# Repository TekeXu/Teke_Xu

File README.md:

Teke Xu
04/01/2016
April Fools' Day!

tama wei sm mei huan hang!!!

                                                    空山新雨后
                                                    天气晚来秋
                                                    明月松间照
                                                    清泉石上流

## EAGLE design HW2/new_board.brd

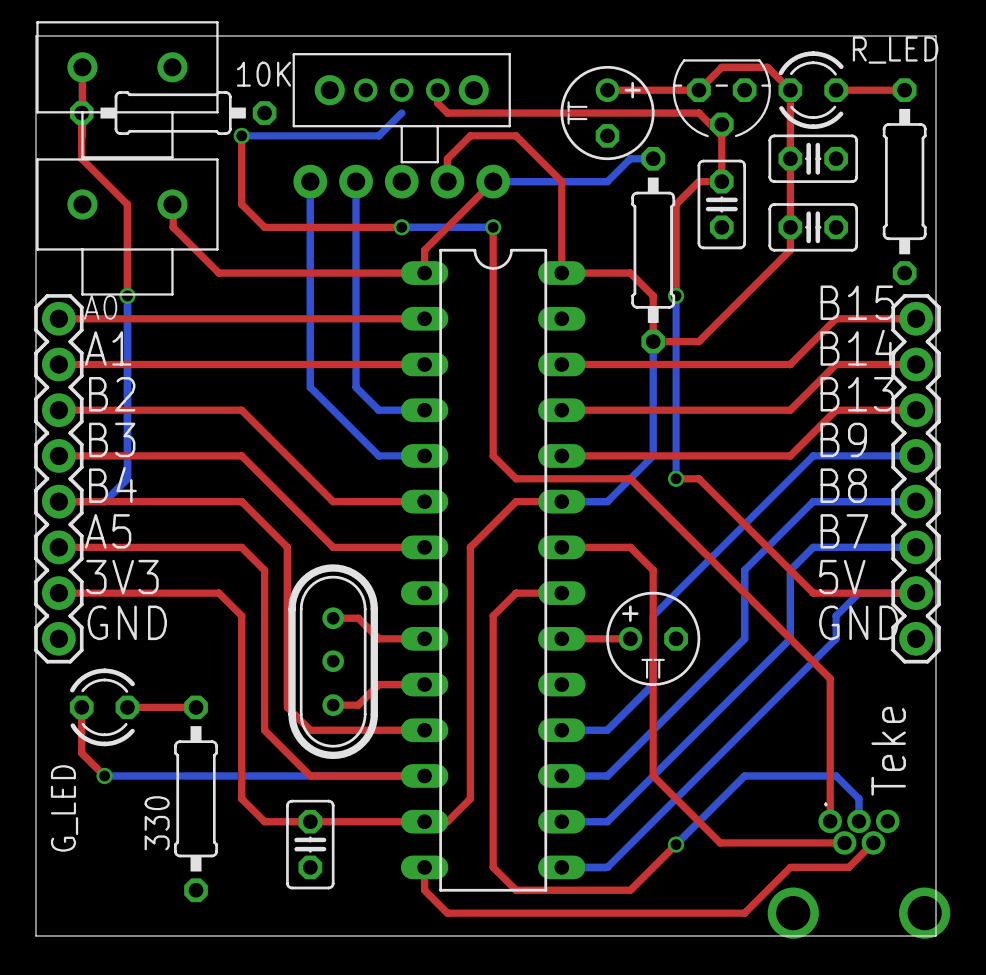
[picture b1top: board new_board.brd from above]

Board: 2 copper layers, 50.0 x 50.0 mm, 22 parts (0 on the bottom side), 27 nets.

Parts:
10K, 330: 0207/10
.: MINI_USB; USB-MB-H
C1, C3, C4, C5: 0.1uF; C025-025X050
C6, C7: 10uF; TT2D5
G_LED: LED3MM
J1: 1X05_NO_SILK
J2, J3: 1X08_ROUND
R2: 330; 0207/10
R4: 10K; 0207/10
R_LED: LED3MM
U$1: PIC32; DIL28-3
U$3: SLIDE_SWITCH
U$4, U$5: PUSH_BUTTON
U$9: MCP1702; TO92
X1: HC49-HC49-3L; HC49-3L

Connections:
+3V3: C1.1, C3.1, C4.1, C7.+, J1.2, J2.7, R4.1, R_LED.A, U$1.13, U$1.23, U$1.28, U$9.3
GND: 10K.2, 330.1, ..GND, C1.2, C3.2, C4.2, C5.2, C6.-, C7.-, J1.3, J2.8, J3.8, R2.1, U$1.8, U$1.19, U$1.27, U$4.P$2, U$5.P$1, U$9.1, X1.2
unnamed: ..ID, U$1.14
unnamed: J1.4, U$1.4
unnamed: J1.5, U$1.5
unnamed: U$1.9, X1.1
unnamed: U$1.10, X1.3
unnamed: 10K.1, J2.5, U$1.11, U$5.P$2
unnamed: R2.2, R_LED.K
unnamed: J1.1, R4.2, U$1.1, U$4.P$1
unnamed: C6.+, U$1.20
unnamed: 330.2, G_LED.K
unnamed: G_LED.A, J2.6, U$1.12
unnamed: ..VBUS, U$3.P$4
unnamed: C5.1, J3.7, U$1.15, U$3.P$3, U$9.2
unnamed: ..D-, U$1.22
unnamed: ..D+, U$1.21
unnamed: J2.1, U$1.2
unnamed: J2.2, U$1.3
unnamed: J2.3, U$1.6
unnamed: J2.4, U$1.7
unnamed: J3.1, U$1.26
unnamed: J3.2, U$1.25
unnamed: J3.3, U$1.24
unnamed: J3.4, U$1.18
unnamed: J3.5, U$1.17
unnamed: J3.6, U$1.16

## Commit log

2016-04-02 My first commit!
2016-04-02 add a line
2016-04-02 main_nothing
2016-04-03 copy
2016-04-03 scratch
2016-04-03 #pragma config
2016-04-03 1kHz
2016-04-03 creat project
2016-04-03 revised
2016-04-03 final_version
2016-04-06 new_schematic
2016-04-07 version_1
2016-04-11 board(layout
2016-04-13 board
2016-04-13 36547576899
2016-04-13 Ready to be checked before order
2016-04-18 example
2016-04-18 to be continued
2016-04-18 3223
2016-04-19 SPI_complete
2016-04-19 revised_SPI
2016-04-20 HW4_completed
2016-04-24 complied
2016-04-24 snapshot
2016-05-05 display_hello
2016-05-10 HW5_print_IMU
2016-05-17 android
2016-06-06 2 hw left
2016-06-08 hw complete
